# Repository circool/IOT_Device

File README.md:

# Universal Smart Home Device

Универсальное устройство для умного дома с поддержкой датчиков температуры/влажности, ШИМ-управления вентилятором, MQTT и веб-интерфейсом. Идеально подходит для автоматизации вытяжной вентиляции в ванной и туалете.

## Особенности

- **Три типа устройств** в одной прошивке:
  - Вентилятор с датчиками (автоматическое управление)
  - Автономный датчик температуры/влажности
  - Управляемый выключатель

- **Smart-управление**:
  - Автоматическое включение по температуре/влажности
  - Ручное управление через MQTT и Web
  - Таймер отложенного включения
  - Аварийное отключение по таймеру

- **Тихий режим (ШИМ)**:
  - Регулировка скорости 0-100%
  - **Адаптивный режим** — автоматическая подстройка мощности
  - Стартовый импульс для надёжного запуска

- **Поддержка платформ**:
  - ESP8266 (NodeMCU, ESP-12F)
  - ESP32 (любые версии)

- **Датчики**:
  - AHT10 (I2C)
  - DHT11/DHT22 (1-Wire)

- **Связь и управление**:
  - MQTT с LWT и autodiscovery-ready топиками
  - Веб-интерфейс для настройки
  - OTA обновления прошивки
  - Точка доступа (AP) для первоначальной настройки
  - Сброс настроек кнопкой / MQTT / Web

- **Надёжность**:
  - Хранение настроек в EEPROM с CRC16
  - Watchdog Timer (WDT)
  - Автоматическое восстановление после потери связи

## Содержание

- [Поддерживаемые устройства](#-поддерживаемые-устройства)
- [Аппаратные требования](#-аппаратные-требования)
- [Схема подключения](#-схема-подключения)
- [Установка прошивки](#-установка-прошивки)
- [Конфигурация](#-конфигурация)
  - [Настройки в коде (config.h)](#-настройки-в-коде-configh)
  - [Настройки в среде (platformio.ini)](#-настройки-в-среде-platformioini)
  - [Файл credentials.h (опционально)](#-файл-credentialsh-опционально)
- [MQTT топики](#-mqtt-топики)
- [Логика работы](#-логика-работы)
- [Компиляция из исходников](#-компиляция-из-исходников)
- [TODO](#-todo)

## Поддерживаемые устройства

| Тип | DEVICE_TYPE | Компоненты | Применение |
|-----|-------------|-----------|------------|
| **Вентилятор** | 1 | Датчик + ШИМ + реле | Вытяжка в ванной/туалете |
| **Датчик** | 2 | Только датчик | Мониторинг микроклимата |
| **Выключатель** | 3 | Реле (без датчика) | Управление освещением/нагрузкой |

## Аппаратные требования

### Компоненты (максимальная конфигурация)

| Компонент | Модель | Примечание |
|-----------|--------|------------|
| Микроконтроллер | ESP8266 (NodeMCU) или ESP32 | Любая плата с WiFi |
| Датчик (опционально) | AHT10 или DHT11/DHT22 | I2C или 1-Wire |
| Исполнительное реле | Твердотельное реле G3MB-202P | Для реализации ШИМ |
| Питание | AC-DC 220V → 3.3V | Подключается параллельно освещению |
| Кнопка управления | Тактовая на замыкание | GPIO0 → GND |
| Светодиод индикации | Любой | С резистором 220-470 Ом (GPIO2* → GND, инверсия) |

### Назначение пинов

| Функция | ESP8266 | ESP32 |
|---------|---------|-------|
| Управление (PWM) | GPIO14 | GPIO4 |
| AHT10 SDA | GPIO4 | GPIO21 |
| AHT10 SCL | GPIO5 | GPIO22 |
| DHT11/22 | GPIO4* | GPIO16* | Однопроводной датчик (GPIO → DATA) |
| Кнопка управления | GPIO0 | GPIO0 |
| Светодиод индикации связи | GPIO2** | GPIO2** |

**Важно:** Для работы ШИМ-регулировки обязательно используйте **твердотельное реле (SSR)**, а не механическое!

**\*** DHT11/22 можно подключать к любым свободным пинам, кроме GPIO0, GPIO2, GPIO15 (ESP8266) из-за особого поведения при загрузке. Рекомендуемые пины: GPIO4, GPIO5, GPIO16 (ESP8266) или GPIO16, GPIO17, GPIO18 (ESP32).

**\*\*** На многих модулях NodeMCU и ESP32-devkit на GPIO2 уже установлен встроенный синий светодиод. При использовании DHT на GPIO2 возникнет конфликт — выберите другой пин для датчика или отключите LED.

## Схема подключения

```
220V AC →→→ AC-DC 3.3V →→→ ESP
           ↓
         Свет
           
220V AC →→→ SSR (реле) →→→ Вентилятор
           ↑
        GPIO (PWM)
           
ESP →→→ I2C →→→ AHT10 (SDA/SCL)
```

**Принцип работы:**
1. Свет включён → устройство получает питание
2. Устройство решает: включать вентилятор или нет (по датчикам)
3. Если нужно — подаёт ШИМ-сигнал на реле
4. Свет выключен → устройство обесточено → вентилятор выключен

## Установка прошивки

### Способ 1: PlatformIO (рекомендуется)

```bash
# Клонировать репозиторий
git clone https://github.com/circool/IOT_Device.git
cd IOT_Device

# Собрать для ESP8266
pio run -e esp8266 -t upload

# Или для ESP32
pio run -e esp32 -t upload
```

### Способ 2: Arduino IDE

1. Установите поддержку ESP8266/ESP32 через Boards Manager
2. Установите библиотеки:
   - PubSubClient by Nick O'Leary
   - Adafruit AHTX0
   - DHT sensor library
   - ElegantOTA
3. Откройте `main.cpp`, выберите плату и загрузите

### Первоначальная настройка

1. **Первый запуск** — устройство создаст точку доступа `Fan_XXXX` (или `Sensor_XXXX`/`Switch_XXXX`)
2. **Подключитесь** к этой WiFi сети (пароль отсутствует)
3. **Откройте браузер** по адресу `http://192.168.4.1`
4. **Заполните настройки:**
   - WiFi SSID и пароль
   - MQTT брокер (адрес и порт)
   - Параметры управления (при необходимости)
5. **Сохраните** — устройство перезагрузится и подключится к вашей сети

## Конфигурация

### Настройки в коде (config.h)

```cpp
// Тип устройства
#define DEVICE_TYPE 1  // 1=Fan, 2=Sensor, 3=Switch

// Датчик (для TYPE 1,2)
#define SENSOR_TYPE 1  // 1=AHT10, 2=DHT

// Аппаратные пины
#define SWITCH_PIN 4     // Пин управления (ESP32)
#define STATUS_LED_PIN 2 // LED индикации (0 = отключён)
#define BUTTON_PIN 0      // Кнопка управления

// Функционал
#define FEATURE_WIFI_ENABLED 1
#define FEATURE_MQTT_ENABLED 1
// #define FEATURE_WEB_ENABLED 1
#define FEATURE_OTA_ENABLED 1
#define FEATURE_WDT_ENABLED 1

// Тайминги
#define WDT_TIMER_MS 5000           // Watchdog таймер
#define WIFI_FALLBACK_TIMEOUT_MS 12000 // Таймаут до перехода в AP

// ШИМ параметры (для TYPE 1)
#define PWM_FREQUENCY 5      // Частота ШИМ (Гц)
#define PWM_RESOLUTION 8     // Разрешение (бит)
#define PWM_STARTING 200     // Стартовый импульс (мс)
#define DEFAULT_SPEED_PERCENT 50 // Скорость по умолчанию (%)

// Адаптивный режим
#define ADAPTIVE_EPSILON_TEMP 0.5   // Чувствительность температуры
#define ADAPTIVE_EPSILON_HUM 2.0    // Чувствительность влажности
#define ADAPTIVE_STEP_SIZE 10       // Шаг адаптации (%)
#define MIN_SPEED_PERCENT 10        // Минимальная скорость при адаптации

// Пороги по умолчанию (для TYPE 1)
#define DEFAULT_LOW_TEMP 27.0
#define DEFAULT_HIGH_TEMP 29.0
#define DEFAULT_LOW_HUM 55.0
#define DEFAULT_HIGH_HUM 60.0
```

### Настройки в среде (platformio.ini)

Файл `platformio.ini` содержит все параметры сборки для разных платформ. Раздел разделён на общие настройки (`[common]`) и специфичные для каждой платформы (`[env:esp32]`, `[env:esp8266]`).

#### Структура файла

```ini
[common]                           # Общие настройки для всех платформ
framework = arduino                # Фреймворк
monitor_speed = 115200             # Скорость Serial порта
upload_speed = 460800              # Скорость загрузки прошивки
build_flags =                      # Флаги компиляции (общие)
    -DMAGIC_VALUE=0x5A6B          # Магическое число для EEPROM
    -DDEVICE_TYPE=1               # Тип устройства (1=Fan, 2=Sensor, 3=Switch)
    -DVERSION=\"1.4\"             # Версия прошивки
    -DSTATUS_LED_PIN=2            # Пин статусного LED (0=отключён)

[env:esp32]                        # Сборка для ESP32
platform = espressif32             # Платформа
board = esp32dev                   # Тип платы
extends = common                   # Наследование общих настроек
lib_deps = ...                     # Зависимости (библиотеки)
build_flags =                      # Специфичные флаги для ESP32
    ${common.build_flags}         # Включить общие флаги
    -DSWITCH_PIN=4                # Пин управления для ESP32
    -DLED_INVERTED=0              # Инверсия LED (0=нормальная логика)

[env:esp8266]                      # Сборка для ESP8266
platform = espressif8266           # Платформа
board = nodemcu                    # Тип платы
extends = common                   # Наследование общих настроек
build_flags = 
    ${common.build_flags}
    -DSWITCH_PIN=14               # Пин управления для ESP8266
    -DLED_INVERTED=1              # Инверсия LED (1=инвертированная)
board_build.flash_size = 4MB      # Размер flash памяти
board_build.flash_mode = dout     # Режим flash (для ESP8266)
```

#### Основные параметры сборки

| Параметр | Значение | Описание |
|----------|----------|----------|
| `-DMAGIC_VALUE` | `0x5A6B` | Идентификатор корректной конфигурации в EEPROM |
| `-DDEVICE_TYPE` | `1`, `2`, `3` | Тип устройства (см. таблицу ниже) |
| `-DVERSION` | `"1.4"` | Версия прошивки (отображается в веб-интерфейсе) |
| `-DSTATUS_LED_PIN` | `2` | Пин для LED индикации (`0` = отключить) |
| `-DSWITCH_PIN` | `4` (ESP32) / `14` (ESP8266) | Пин управления реле/вентилятором |
| `-DLED_INVERTED` | `0` или `1` | Инверсия логики LED (`1` = HIGH выключает) |

#### Типы устройств (DEVICE_TYPE)

```ini
# Вентилятор с датчиками (полная функциональность)
-DDEVICE_TYPE=1

# Только датчик (без управления нагрузкой)
-DDEVICE_TYPE=2

# Управляемый выключатель (без датчика)
-DDEVICE_TYPE=3
```

#### Включение/отключение функционала

```ini
# Основные модули (по умолчанию ВСЕ включены)
-DFEATURE_WIFI_ENABLED=1          # WiFi поддержка
-DFEATURE_MQTT_ENABLED=1          # MQTT клиент
; -DFEATURE_WEB_STATUS_ENABLED=1           # Веб-сервер c отображением состояния устройства
-DFEATURE_OTA_ENABLED=1           # OTA обновления
-DFEATURE_WDT_ENABLED=1           # Watchdog Timer

# Отключение ненужного функционала (экономия памяти)
; -DFEATURE_MQTT_ENABLED=0        # Пример отключения MQTT
; -DFEATURE_WIFI_ENABLED=0        # Полностью отключить WiFi
; -DFEATURE_WDT_ENABLED=0         # Отключить Watchdog (только для отладки)
```

#### Настройка отладки (логирование)

```ini
# Глобальное включение отладки
-DDEBUG_ENABLED=1

# Детальное логирование компонентов (работает только при DEBUG_ENABLED=1)
-DXLOG_SENSOR=1            # Логи датчика
-DXLOG_CONFIG=1            # Логи конфигурации
-DXLOG_FAN=1               # Логи вентилятора
-DXLOG_MQTT=1              # Логи MQTT
-DXLOG_WIFI=1              # Логи WiFi
-DXLOG_WEB=1               # Логи веб-сервера
-DXLOG_AP=1                # Логи режима точки доступа
-DXLOG_OTA=1               # Логи OTA обновлений
-DXLOG_LED=1               # Логи LED индикации
```

**Пример включения полной отладки:**
```ini
build_flags =
    ${common.build_flags}
    -DDEBUG_ENABLED=1
    -DXLOG_SENSOR=1
    -DXLOG_MQTT=1
    -DXLOG_WIFI=1
```

#### Настройка MQTT функционала

```ini
# MQTT возможности (требуют FEATURE_MQTT_ENABLED=1)
-DMQTT_RESET_ENABLED=1            # Разрешить сброс через MQTT
-DMQTT_PUBLISH_RSSI=1             # Публиковать RSSI WiFi
-DMQTT_PUBLISH_RESET_REASON=1     # Публиковать причину перезагрузки
-DMQTT_IGNORE_PUBLISH_NORMAL_RESET_REASONS=1  # Не публиковать штатные перезагрузки

# Настройки MQTT соединения
-DMQTT_RECONNECT_DELAY_MS=5000    # Задержка переподключения (мс)
-DMQTT_KEEPALIVE_SEC=3            # Keepalive интервал (сек)
```

#### Настройка веб-интерфейса

```ini
# WEB возможности (требуют FEATURE_WEB_ENABLED=1)
-DFEATURE_WEB_STATUS_ENABLED=1    # Страница статуса
-DWEB_SHOW_RSSI=1                 # Отображать RSSI на странице
-DWEB_RESET_ENABLED=1             # Кнопка управления в веб-интерфейсе

# Настройки точки доступа (AP)
-DWIFI_FALLBACK_TIMEOUT_MS=12000    # Таймаут до перехода в AP (мс)
-DAP_IP_ADDRESS="192.168.4.1"     # IP адрес в режиме AP
```

#### Настройки Watchdog (WDT)

```ini
# Параметры Watchdog (требуют FEATURE_WDT_ENABLED=1)
-DWDT_TIMER_MS=5000               # Таймаут WDT (мс)
-DLOOP_WATCHDOG_MULTIPLIER=3      # Множитель для основного цикла
```

#### Настройки датчиков

```ini
# Тип датчика (для DEVICE_TYPE=1 или 2)
-DSENSOR_TYPE=1                   # 1 = AHT10 (I2C), 2 = DHT11/22 (GPIO)

# Параметры для DHT (если SENSOR_TYPE=2)
-DSENSOR_PIN=2                    # GPIO пин для DHT
-DDHT_TYPE=DHT11                  # Тип DHT (DHT11, DHT22, DHT21)

# Интервал опроса датчика (сек)
-DDEFAULT_SENSOR_DURATION=10
```

#### Настройки ШИМ (для вентилятора)

```ini
# ШИМ параметры (для DEVICE_TYPE=1)
-DPWM_ENABLED=1                   # Включить ШИМ
-DPWM_FREQUENCY=5                 # Частота ШИМ (Гц) — 5 Гц оптимально для SSR
-DPWM_RESOLUTION=8                # Разрешение ШИМ (бит) — 8 бит = 0-255
-DPWM_STARTING=200                # Длительность стартового импульса (мс)

# Адаптивный режим (требует PWM_ENABLED=1)
-DAPAPTIVE_ENABLED=1              # Включить адаптивный режим
-DDEFAULT_SPEED_PERCENT=50        # Скорость по умолчанию (%)
-DMIN_SPEED_PERCENT=10            # Минимальная скорость при адаптации
-DADAPTIVE_EPSILON_TEMP=0.5       # Чувствительность температуры (°C)
-DADAPTIVE_EPSILON_HUM=2.0        # Чувствительность влажности (%)
-DADAPTIVE_STEP_SIZE=10           # Шаг изменения скорости (%)
-DADAPTIVE_SPEED_SENSITIVITY=0.7  # Чувствительность к скорости изменения
```

#### Настройки аварийной защиты

```ini
# Таймеры безопасности (для DEVICE_TYPE=1 или 3)
-DEMERGENCY_ENABLED=1             # Включить аварийное отключение
-DMAX_ON_TIME_SEC=3600            # Максимальное время работы (сек) — 1 час

# Таймер отложенного включения
-DDEFAULT_DELAY_SECONDS=60        # Задержка по умолчанию (сек)
-DDEFAULT_BOOT_SWITCH_STATE=0             # Состояние при старте (0=выкл, 1=вкл)
```

#### Настройки WiFi

```ini
# Параметры WiFi (требуют FEATURE_WIFI_ENABLED=1)
-DWIFI_CONNECT_TIMEOUT_MS=30000   # Таймаут подключения (мс)
-DWIFI_OUTPUT_POWER=15.0          # Мощность передатчика (0-20.5 dBm)

# Включить сканирование сетей при старте (только для отладки)
; -DSCANNING_WIFI_ENABLED=1
```

#### Примеры готовых конфигураций

**1. Минимальная конфигурация (только датчик, без WiFi):**
```ini
[env:esp32]
build_flags =
    -DDEVICE_TYPE=2
    -DWIFI_ENABLED=0
    -DMQTT_ENABLED=0
    ; -FEATURE_WEB_ENABLED=0
    -DSENSOR_TYPE=1
    -DSTATUS_LED_PIN=0
```

**2. Полная конфигурация с отладкой:**
```ini
[env:esp32]
build_flags =
    ${common.build_flags}
    -DDEBUG_ENABLED=1
    -DXLOG_SENSOR=1
    -DXLOG_MQTT=1
    -DXLOG_WIFI=1
    -DMQTT_PUBLISH_RSSI=1
    -DWEB_SHOW_RSSI=1
```

**3. Выключатель с таймером (без датчика):**
```ini
[env:esp8266]
build_flags =
    ${common.build_flags}
    -DDEVICE_TYPE=3
    -DSWITCH_PIN=14
    -DDEFAULT_DELAY_SECONDS=30
    -DMAX_ON_TIME_SEC=1800
    -DDEFAULT_BOOT_SWITCH_STATE=0
```

**4. Тихий режим с адаптацией:**
```ini
[env:esp32]
build_flags =
    ${common.build_flags}
    -DDEVICE_TYPE=1
    -DPWM_ENABLED=1
    -DAPAPTIVE_ENABLED=1
    -DPWM_FREQUENCY=5
    -DDEFAULT_SPEED_PERCENT=70
    -DMIN_SPEED_PERCENT=20
    -DADAPTIVE_STEP_SIZE=5
```

#### Важные замечания

1. **Приоритет флагов:** Специфичные для платформы флаги переопределяют общие
2. **Экономия памяти:** Отключайте ненужный функционал (`FEATURE_MQTT_ENABLED=0`, `WEB_ENABLED=0`) для ESP8266 (особенно важно при ограниченной flash)
3. **Частота ШИМ:** Для твердотельных реле оптимальна 5-10 Гц. Более высокая частота может вызвать перегрев реле
4. **ESP8266 нюансы:**
   - Требуется `-Wno-sign-compare` и `-Wno-uninitialized` для подавления предупреждений
   - Режим flash `dout` обязателен для некоторых плат
   - LED часто инвертирован (`LED_INVERTED=1`)

#### Изменение параметров без перекомпиляции

Некоторые параметры можно изменить через веб-интерфейс или MQTT без перепрошивки:
- Пороги температуры/влажности
- Скорость вентилятора
- Таймеры (задержка, аварийное отключение)
- Режимы работы (ручной/автоматический)

Параметры, требующие перекомпиляции:
- Тип устройства (`DEVICE_TYPE`)
- Назначение пинов (`SWITCH_PIN`, `STATUS_LED_PIN`)
- Частота ШИМ (`PWM_FREQUENCY`)
- Включение/отключение модулей (`FEATURE_MQTT_ENABLED`, `WEB_ENABLED`)
```

### Файл credentials.h (опционально)

Создайте этот файл для заводских настроек:

```cpp
// credentials.h
#define WIFI_SSID "MyWiFi"
#define WIFI_PASSWORD "MyPassword"
#define MQTT_BROKER "192.168.1.100"
#define MQTT_PORT 1883
#define MQTT_USER "user"
#define MQTT_PASSWORD "pass"
```

## MQTT топики

Устройство использует префикс вида `{Type}_{ID}` (например `Fan_D84C`).

### Общие топики

| Топик | Направление | Формат | Описание |
|-------|------------|--------|----------|
| `{prefix}/status` | Dev → Broker | `Online`/`Offline` | Статус (LWT) |
| `{prefix}/version` | Dev → Broker | `1.4` | Версия прошивки |
| `{prefix}/c/system/reset` | Broker → Dev | `1` | Сброс настроек |

### Для вентилятора (TYPE 1)

| Топик | Направление | Описание |
|-------|------------|----------|
| `{prefix}/fan/state` | Dev → Broker | `ON`/`OFF` |
| `{prefix}/c/fan/state` | Broker → Dev | Управление |
| `{prefix}/fan/speed` | Dev → Broker | Скорость (0-100%) |
| `{prefix}/c/fan/speed` | Broker → Dev | Установка скорости |
| `{prefix}/fan/adaptiveMode` | Dev → Broker | Адаптивный режим |
| `{prefix}/fan/delaySec` | Dev → Broker | Задержка включения |
| `{prefix}/fan/maxOnTime` | Dev → Broker | Аварийное отключение |
| `{prefix}/fan/sensorMode` | Dev → Broker | Режим датчика |
| `{prefix}/sensor/temperature` | Dev → Broker | Температура |
| `{prefix}/sensor/humidity` | Dev → Broker | Влажность |
| `{prefix}/sensor/lowTemp` | Dev → Broker | Нижний порог T |
| `{prefix}/c/sensor/highTemp` | Broker → Dev | Верхний порог T |

### Для датчика (TYPE 2)

| Топик | Направление | Описание |
|-------|------------|----------|
| `{prefix}/sensor/temperature` | Dev → Broker | Температура |
| `{prefix}/sensor/humidity` | Dev → Broker | Влажность |

### Для выключателя (TYPE 3)

| Топик | Направление | Описание |
|-------|------------|----------|
| `{prefix}/switch/state` | Dev → Broker | Состояние |
| `{prefix}/c/switch/state` | Broker → Dev | Управление |
| `{prefix}/switch/delaySec` | Dev → Broker | Задержка включения |
| `{prefix}/switch/maxOnTime` | Dev → Broker | Аварийное отключение |

## Логика работы

### Режимы работы

1. **Режим датчика** (`sensorMode = 1`):
   - Включение: температура ≥ `highTemp` **ИЛИ** влажность ≥ `highHum`
   - Выключение: температура ≤ `lowTemp` **И** влажность ≤ `lowHum`

2. **Ручной режим** (`sensorMode = 0`):
   - Игнорирует датчик
   - Управление только через MQTT/Web

3. **Адаптивный режим** (при `speedPercent < 100`):
   - Автоматически повышает/понижает скорость
   - Старается удержать температуру/влажность на уровне момента включения

### Таймеры

- **Отложенное включение** (`delaySeconds`):
  - Запускается при выключении вентилятора
  - По истечении — принудительное включение

- **Аварийное отключение** (`maxOnTime`):
  - Защита от перегрева
  - По истечении — выключение + переход в ручной режим

### Приоритеты команд

1. **Ручное управление** (MQTT/Web) — наивысший приоритет
2. **Таймер отложенного включения**
3. **Режим управления датчиком**

## Компиляция из исходников

### Структура проекта

```
├── main.cpp           # Основной цикл
├── config.h/cpp       # Настройки и EEPROM
├── mqtt_manager.h/cpp         # MQTT клиент
├── web_manager.h/cpp          # Веб-сервер
├── sensor.h/cpp       # Датчики
├── fan.h/cpp          # Управление вентилятором
├── switch.h/cpp       # Управление выключателем
├── led_manager.h/cpp          # LED индикация
├── ansi.h             # Цветной вывод в Serial
├── web_strings.h      # HTML строки
└── platformio.ini     # Конфигурация сборки
```

### PlatformIO конфигурация

```ini
[env:esp32]
platform = espressif32
board = esp32dev
build_flags = 
    -DDEVICE_TYPE=1
    -DMQTT_ENABLED=1
    ; -FEATURE_WEB_ENABLED=1
lib_deps = 
    knolleary/PubSubClient @ ^2.8
    adafruit/Adafruit AHTX0 @ ^2.0.5
    ayushsharma82/ElegantOTA @ ^2.2.8
    adafruit/DHT sensor library@^1.4.6
```

### Предупреждение относительно OTA

**ESP8266 с 1MB flash (ESP-01, ESP-07) не поддерживают OTA!**
Несмотря на то, что веб-интерфейс ElegantOTA показывает успешную загрузку, после перезагрузки устройство останется на старой прошивке. Для OTA требуется минимум **2MB flash**. Используйте модули с 4MB (NodeMCU, Wemos D1 mini, ESP-12F) или установите константу/флаг `FEATURE_OTA_ENABLED=0` / `-DFEATURE_OTA_ENABLED=0` для исключения OTA.

### Отладка

```cpp
// В platformio.ini
build_flags = 
    -DDEBUG_ENABLED=1           // Включить отладку
    -DXLOG_SENSOR=1              // Логи датчика
    -DXLOG_MQTT=1                // Логи MQTT
    -DXLOG_WIFI=1                // Логи WiFi
    -DXLOG_WEB=1                 // Логи Web
```

## TODO

- [ ] Реализовать MQTT Discovery для Home Assistant
- [ ] Добавить поддержку ESP32-C6 (ZigBee/Matter)

---

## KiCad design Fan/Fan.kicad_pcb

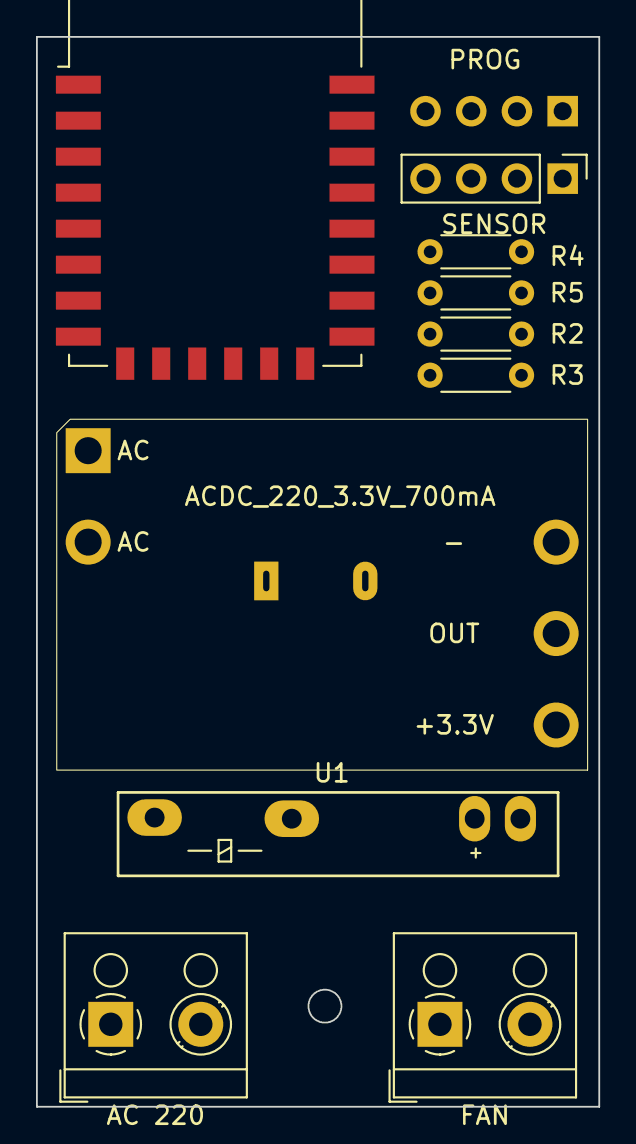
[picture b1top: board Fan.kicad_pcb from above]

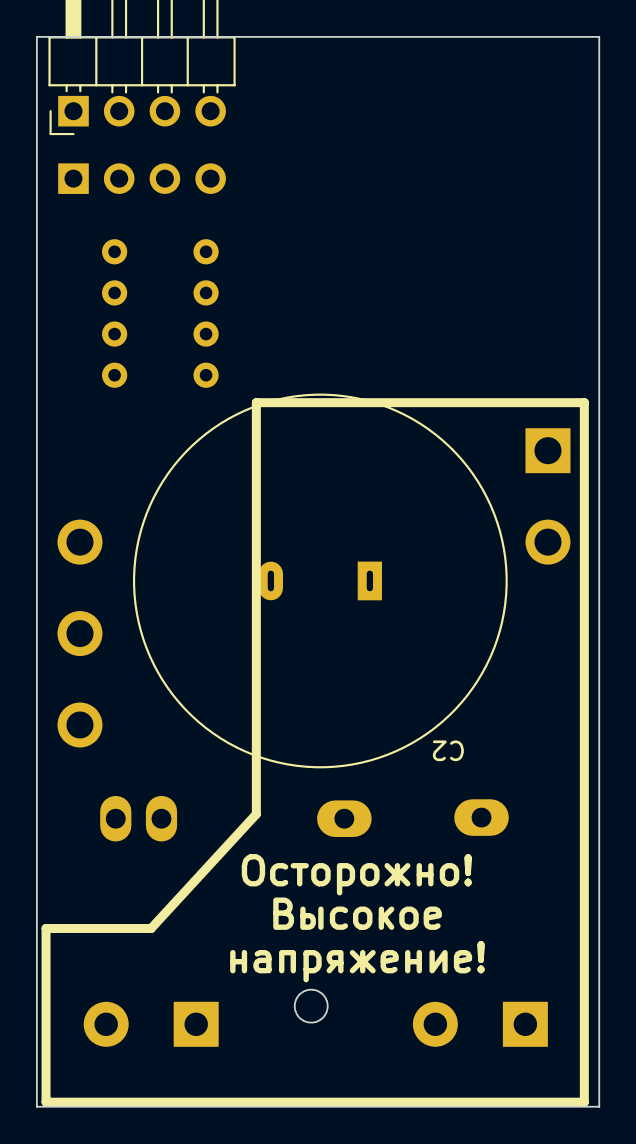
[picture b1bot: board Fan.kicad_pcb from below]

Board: 2 copper layers, 31.2 x 59.4 mm, 12 parts (2 on the bottom side), 12 nets, no tracks yet.

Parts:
C2: 4F; C_Radial_D20.4mm_H7.0mm_P6.8mm
J1: PROG; PinHeader_1x04_P2.54mm_Horizontal
J2: SENSOR; PinHeader_1x04_P2.54mm_Vertical
M1: ACDC_220_3.3V_700mA; Converter_ADCD_China
R2, R3, R4, R5: 10K; R_Axial_DIN0204_L3.6mm_D1.6mm_P5.08mm_Horizontal
SW1: AC 220; TerminalBlock_RND_205-00001_1x02_P5.00mm_Horizontal
SW2: FAN; TerminalBlock_RND_205-00001_1x02_P5.00mm_Horizontal
U1: G5MB-202P; Relay_SPDT_Omron-G3MB
U2: ESP-12F; ESP-12E

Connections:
/RXD: J1.4, U2.21 (GPIO3/RXD)
/SCL: J2.4, U2.20 (GPIO5)
/SDA: J2.2, U2.19 (GPIO4)
/TXD: J1.3, U2.22 (GPIO1/TXD)
AC: M1.1 (AC(L)), M1.2 (AC(N)), SW1.1, SW1.2, SW2.1, U1.1
GND: C2.2, J1.2, J2.3, M1.6 (Vout-), R5.2, U1.4, U2.15 (GND)
unnamed: R3.2, U2.1 (~RST)
unnamed: R4.2, U2.3 (EN)
unnamed: R5.1, U2.16 (GPIO15)
unnamed: SW2.2, U1.2
unnamed: U1.3, U2.5 (GPIO14)
VCC: J1.1, J2.1, M1.8 (Vout+), R2.1, R3.1, R4.1, U2.8 (VCC)

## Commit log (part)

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2024-01-23 prepare enviropment
2024-01-28 Update main.cpp
    Пример датчика температуры и влажности AHT10
2024-01-28 Update main.cpp
    Предварительная реализация универсального класса Sensor
2024-01-29 Update main.cpp
    прототип
2024-01-29 Update main.cpp
    начало работы с EEPROM
2024-01-30 Update main.cpp
    прототип EEPROM_FEATURE
2024-01-30 Update main.cpp
    Инициализация предварительно
2024-01-30 Update main.cpp
    Прототип (датчик+выключатель)
2024-01-31 Update main.cpp
    Прототип (датчик+выключатель+OTA)
2024-01-31 Update main.cpp
    bugfix: исправлена ошибка в определении факта изменения показаний датчика температуры/влажности
2024-01-31 Delete SensorTemperatureHumidity.h
    Удаление мусора
2024-01-31 Update main.cpp
    Изменение в методах получения показаний датчика температуры/влажности
2024-01-31 Update main.cpp
    8266 OTA
2024-01-31 ESP8266+ESP32
    SENSOR+RELAY+OTA
2024-10-10 New params
    Added seme params to config
2026-05-06 ver 0.1
    first stage commit
2026-05-07 ver 0.2
    Presumably working version
2026-05-08 some errors fix
    Before logic refactoring
2026-05-08 cleaning after refactoring
2026-05-08 bugfixes
2026-05-09 bugfix
    -captive 8266
    +mac in wifi/mqtt_id
2026-05-12 bbugfix
2026-05-12 Adaptive fan speed
    Automatic speed adjust for device type 1
    Some bug fixes
    Some refactors
2026-05-13 fan: speed-based adaptive step
    scale adaptive PWM step by rate of humidity change
2026-05-14 prototype
2026-05-27 prototype v. 1.0
2026-05-27 Update fp-info-cache
2026-05-29 bugfix
2026-05-31 prototype 1.2
2026-05-31 web refactoring
    decrease size, remove Strings
2026-06-01 web refactoring
    ESP32 too
2026-06-01 DEBUG_WIFI_ENABLED bugfix for ESP32
2026-06-01 Update PROJECT.md
    TODO update
2026-06-01 bugfix LED/DHT pins
2026-06-01 bugfix
    manual mode depend sensor error
    web buttons
2026-06-01 ESP32 OTA bugfix
2026-06-01 some visual enhancement for logging
2026-06-02 prototype 1.3
    remove logging in production mode
2026-06-03 minor fixes
2026-06-04 fan adaptive logic fix
2026-06-04 espressif32 downgrade
2026-06-04 web harmonize
2026-06-05 refactor(mqtt): isolate MQTTManager from global config and state
    - MQTTManager.begin() now accepts explicit parameters
    - Removed publishConfig() - initial config published from main.cpp
    - MQTTManager no longer reads config.*, currentTemp, currentHum, fanOn
    - Added state tracking in loop() for all config parameters
    - Fixed misleading 'Connection lost' message on first connect
    - Disabled CORE_DEBUG_LEVEL=5 for cleaner logs
2026-06-05 refactor(web): remove staticConfig, read EEPROM directly for settings page
    - Remove global staticConfig variable (saves 356 bytes RAM)
    - Add config_getSaved() to read config from EEPROM on demand
    - Web config page now reads saved settings via config_getSaved()
    - Web status page continues using current runtime config (global config)
    - Fan restores speed from saved settings using config_getSaved()
    - Remove staticConfig copy from config_write()
2026-06-05 refactor(web): full encapsulation, remove staticConfig
    - Remove global staticConfig variable (saves 356 bytes RAM)
    - Add config_getSaved() to read saved settings from EEPROM on demand
    - Move all status page HTML generation from template to web_buildStatusHtml()
    - Template renderStatusPage() now receives ready-made status HTML string
    - Template renderConfigPage() now receives all data as parameters (savedConfig, currentMode, currentSsid, currentIp)
    - Web no longer depends on mqtt.h, sensor.h, fan.h, switch.h directly
2026-06-05 remove async webserver for ESP32
2026-06-06 refactor(config)
    инкапсуляция конфигурации через геттеры/сеттеры
2026-06-06 refactor(sensor): инкапсуляция датчика через геттеры
    - Удалены глобальные переменные currentTemp, currentHum, sensorOk, sensorError, humRate
    - Добавлен API: sensor_getTemperature(), sensor_getHumidity(), sensor_isOk(),
    sensor_getError(), sensor_getHumRate()
    - sensor_read() заменён на sensor_update() с возвратом bool
    - Все модули (fan, main, web) переведены на новый API
2026-06-06 refactor(actuator): объединение fan/switch в единый актуатор
    - Создан ActuatorBase с общей логикой (таймер, maxOnTime)
    - FanActuator наследует ActuatorBase, добавляет ШИМ и адаптацию
    - SwitchActuator наследует ActuatorBase (только вкл/выкл)
    - Инкапсуляция: геттеры/сеттеры для состояния и скорости
    - Удалены старые файлы fan.cpp, fan.h, switch.cpp, switch.h
    Тестирование: MQTT команды работают, таймер включения/выключения работает,
2026-06-07 fix(web): адаптация под новый API актуатора
    В предыдущем коммите (refactor(actuator)) были удалены глобальные функции
    fan_getState(), fan_set(), fan_setOverrideMode(), но web.cpp продолжал их использовать.
    Заменены вызовы:
    - fan_getState() → fan.getState()
    - fan_set() → fan.set(..., true)
    - fan_setOverrideMode() → config_setSensorControlMode() + fan.setAdaptiveMode()
2026-06-07 added annotations
2026-06-07 fix(actuator): приведение алгоритмов к заданной логике
    - Добавлен onManualCommandCallback в ActuatorBase
    - Переписан set() — сначала режим, потом состояние
    - Таймер теперь вызывает set(true, true) для переключения режима
    - Убран дублирующий вызов config_setSensorControlMode(false) из web.cpp
    - FanActuator реализует колбэк для установки sensorControlMode=false
    - Добавлены комментарии отладки для web
2026-06-07 fix(fan/sensor)
    Возврат логики управления сенсором
2026-06-07 fix (mqtt) Публикация версии
2026-06-07 refactor(web): удалён DNSServer, унифицирован AP режим
    - Удалён DNSServer для ESP8266
    - Унифицирована инициализация AP: общие обработчики вынесены за #ifdef
    - Добавлен лог запуска сервера в AP режиме
    - Упрощён web_update() до server.handleClient()
2026-06-08 fix (multiple)
    TODO fix:
    [+] Удалить дублирование кода для getResetReason()
    [+] Исправить: для типа 2/3 ошибки в названиях топиков.
    [+] В web нет отображения оставшегося времени и состояния таймеров
    [+] Исправить отсутствие публикации MQTT значений для датчика и выключателя, rssi, версии и др
2026-06-08 fix(для maxOnTime,delaySeconds)
    [+] В web нет отображения оставшегося времени и состояния таймеров
    fix: переход в ручной режим отключает Режим управления таймером
2026-06-09 led EMERGENCY_STOP
2026-06-09 remove magics
2026-06-09 refactor: вынести WiFi и OTA в отдельные слои
    - Создан wifi_manager.h/cpp — слой управления WiFi (подключение, AP, RSSI, IP)
    - Создан ota.h/cpp — слой обновления прошивки (ElegantOTA)
    - Устранены циклические зависимости: wifi_manager теперь не знает о web
    - Исправлен порядок включения заголовков для корректной компиляции ESP32/ESP8266
    - Убраны дублирования #include и диагностические pragma
    - web_templates.h теперь использует ota_is_available() вместо w
2026-06-09 fix (6266)
2026-06-09 wdt as layer
2026-06-10 fix (web config)
    - для ESP32 буферизировать вывод для ускорения отображения страницы
    - мелкие правки
    - только конфигурация в режиме AP на /
2026-06-11 clear (web)
2026-06-11 logger
2026-06-11 remove amsi.h
2026-06-11 ref (led)
2026-06-11 clear (mqtt)
2026-06-11 ref (led and wifi manager)
2026-06-12 (fix) log formatting
2026-06-12 (clear) remove comments
2026-06-12 (ref) moving wifi scan to manager
2026-06-12 (fix) web
    status page adding emergency stop
2026-06-12 fix (web)
    correct typewrites
2026-06-13 upd (remove debug)
    форматирование кода
    блок LED перемещен в начало цикла
    исправлены приоритеты для LED
    устранена задержка в AP режиме - для чистой индикации LED
2026-06-13 fix (add not initialized variables)
    FanActuator::_rampUpActive
    FanActuator::_lastRampUpTime
    MQTTManager::_clientId'
2026-06-13 remove debugs
2026-06-13 rename defaults
2026-06-13 fix (logger)
2026-06-13 upd (todo mqtt)
    [x] Расширить понимаемые значения для MQTT reset
2026-06-14 upd (add comments)
2026-06-14 fix (config)
    remove debug tails
2026-06-14 fix (remove debug tails)
2026-06-14 fix (remove magic)
2026-06-14 formatting
2026-06-14 upd (ic2)
    кастомные пины для I2C
2026-06-14 clear (led)
    удаление избыточных директив препроцессора для слоя LED
2026-06-14 clear (web)
    Удаление возможности сброса настроек посредством web интерфейса
2026-06-14 clear (wipi power)
    Удалена регулировка мощности сигнала wifi
2026-06-14 clear (web)
    удаление избыточных директив препроцессора для слоя WEB
2026-06-14 fix (OTA)
    clean - remove isOtaAvailable()/ota_set_available()/ota_available
2026-06-14 format and doxygen add
2026-06-14 doxygen add
2026-06-14 upd (led)
    Slow blink every second
2026-06-15 Refactor: универсальная архитектура с поддержкой транспортов

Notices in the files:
README.md:
License: MIT
